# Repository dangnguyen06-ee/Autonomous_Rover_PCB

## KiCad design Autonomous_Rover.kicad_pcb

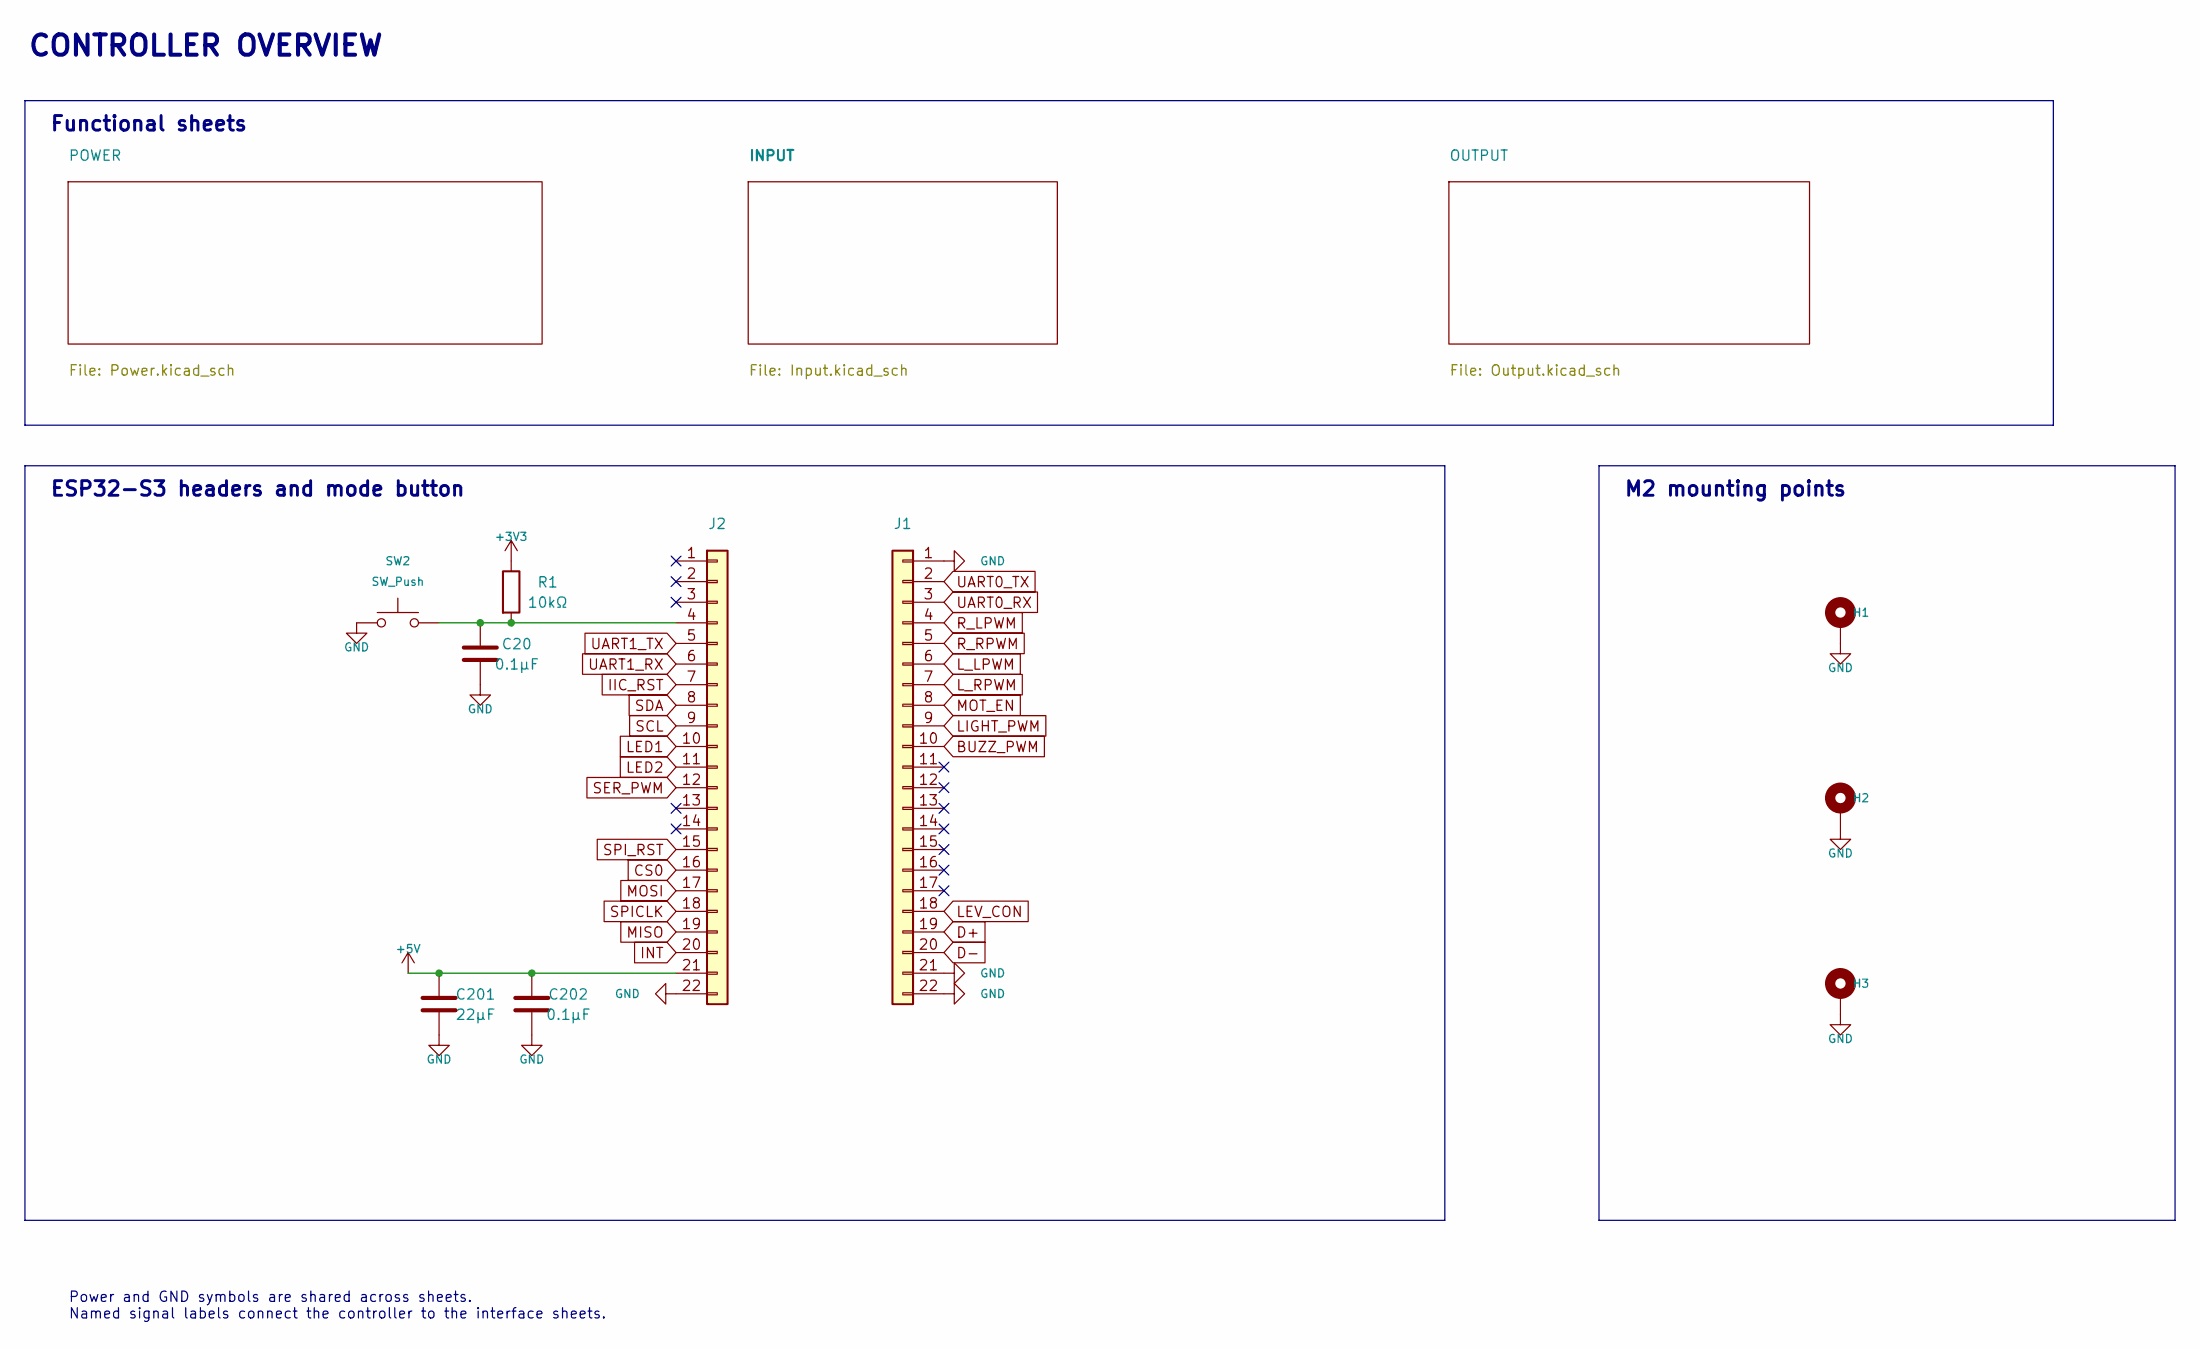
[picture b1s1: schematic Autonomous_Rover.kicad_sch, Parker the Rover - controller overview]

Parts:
C20, C202: 0.1µF; C_0805_2012Metric_Pad1.18x1.45mm_HandSolder
C201: 22µF; C_0805_2012Metric_Pad1.18x1.45mm_HandSolder
H1, H2, H3: M2; MountingHole_2.2mm_M2_ISO7380_Pad
J1: ESP32_R; PinSocket_1x22_P2.54mm_Vertical
J2: ESP32_L; PinSocket_1x22_P2.54mm_Vertical
R1: 10kΩ; R_0805_2012Metric_Pad1.20x1.40mm_HandSolder
SW2: SW_Push; SW_SPST_TS-1088-xR020

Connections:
+3V3: R1.1; also elsewhere on the board
+5V: C201.2, C202.2, J2.21; also elsewhere on the board
BUZZ_PWM: J1.10; also elsewhere on the board
CS0: J2.16; also elsewhere on the board
D+: J1.19; also elsewhere on the board
D-: J1.20; also elsewhere on the board
GND: C20.1, C201.1, C202.1, H1.1 (1_1), H2.1 (1_1), H3.1 (1_1), J1.1, J1.21, J1.22, J2.22, SW2.1; also elsewhere on the board
IIC_RST: J2.7; also elsewhere on the board
INT: J2.20; also elsewhere on the board
LED1: J2.10; also elsewhere on the board
LED2: J2.11; also elsewhere on the board
LEV_CON: J1.18; also elsewhere on the board
LIGHT_PWM: J1.9; also elsewhere on the board
L_LPWM: J1.6; also elsewhere on the board
L_RPWM: J1.7; also elsewhere on the board
MISO: J2.19; also elsewhere on the board
MOSI: J2.17; also elsewhere on the board
MOT_EN: J1.8; also elsewhere on the board
unnamed: C20.2, J2.4, R1.2, SW2.2
R_LPWM: J1.4; also elsewhere on the board
R_RPWM: J1.5; also elsewhere on the board
SCL: J2.9; also elsewhere on the board
SDA: J2.8; also elsewhere on the board
SER_PWM: J2.12; also elsewhere on the board
SPICLK: J2.18; also elsewhere on the board
SPI_RST: J2.15; also elsewhere on the board
UART0_RX: J1.3; also elsewhere on the board
UART0_TX: J1.2; also elsewhere on the board
UART1_RX: J2.6; also elsewhere on the board
UART1_TX: J2.5; also elsewhere on the board

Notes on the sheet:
M2 mounting points
Functional sheets
ESP32-S3 headers and mode button
CONTROLLER OVERVIEW
Power and GND symbols are shared across sheets. Named signal labels connect the controller to the interface sheets.

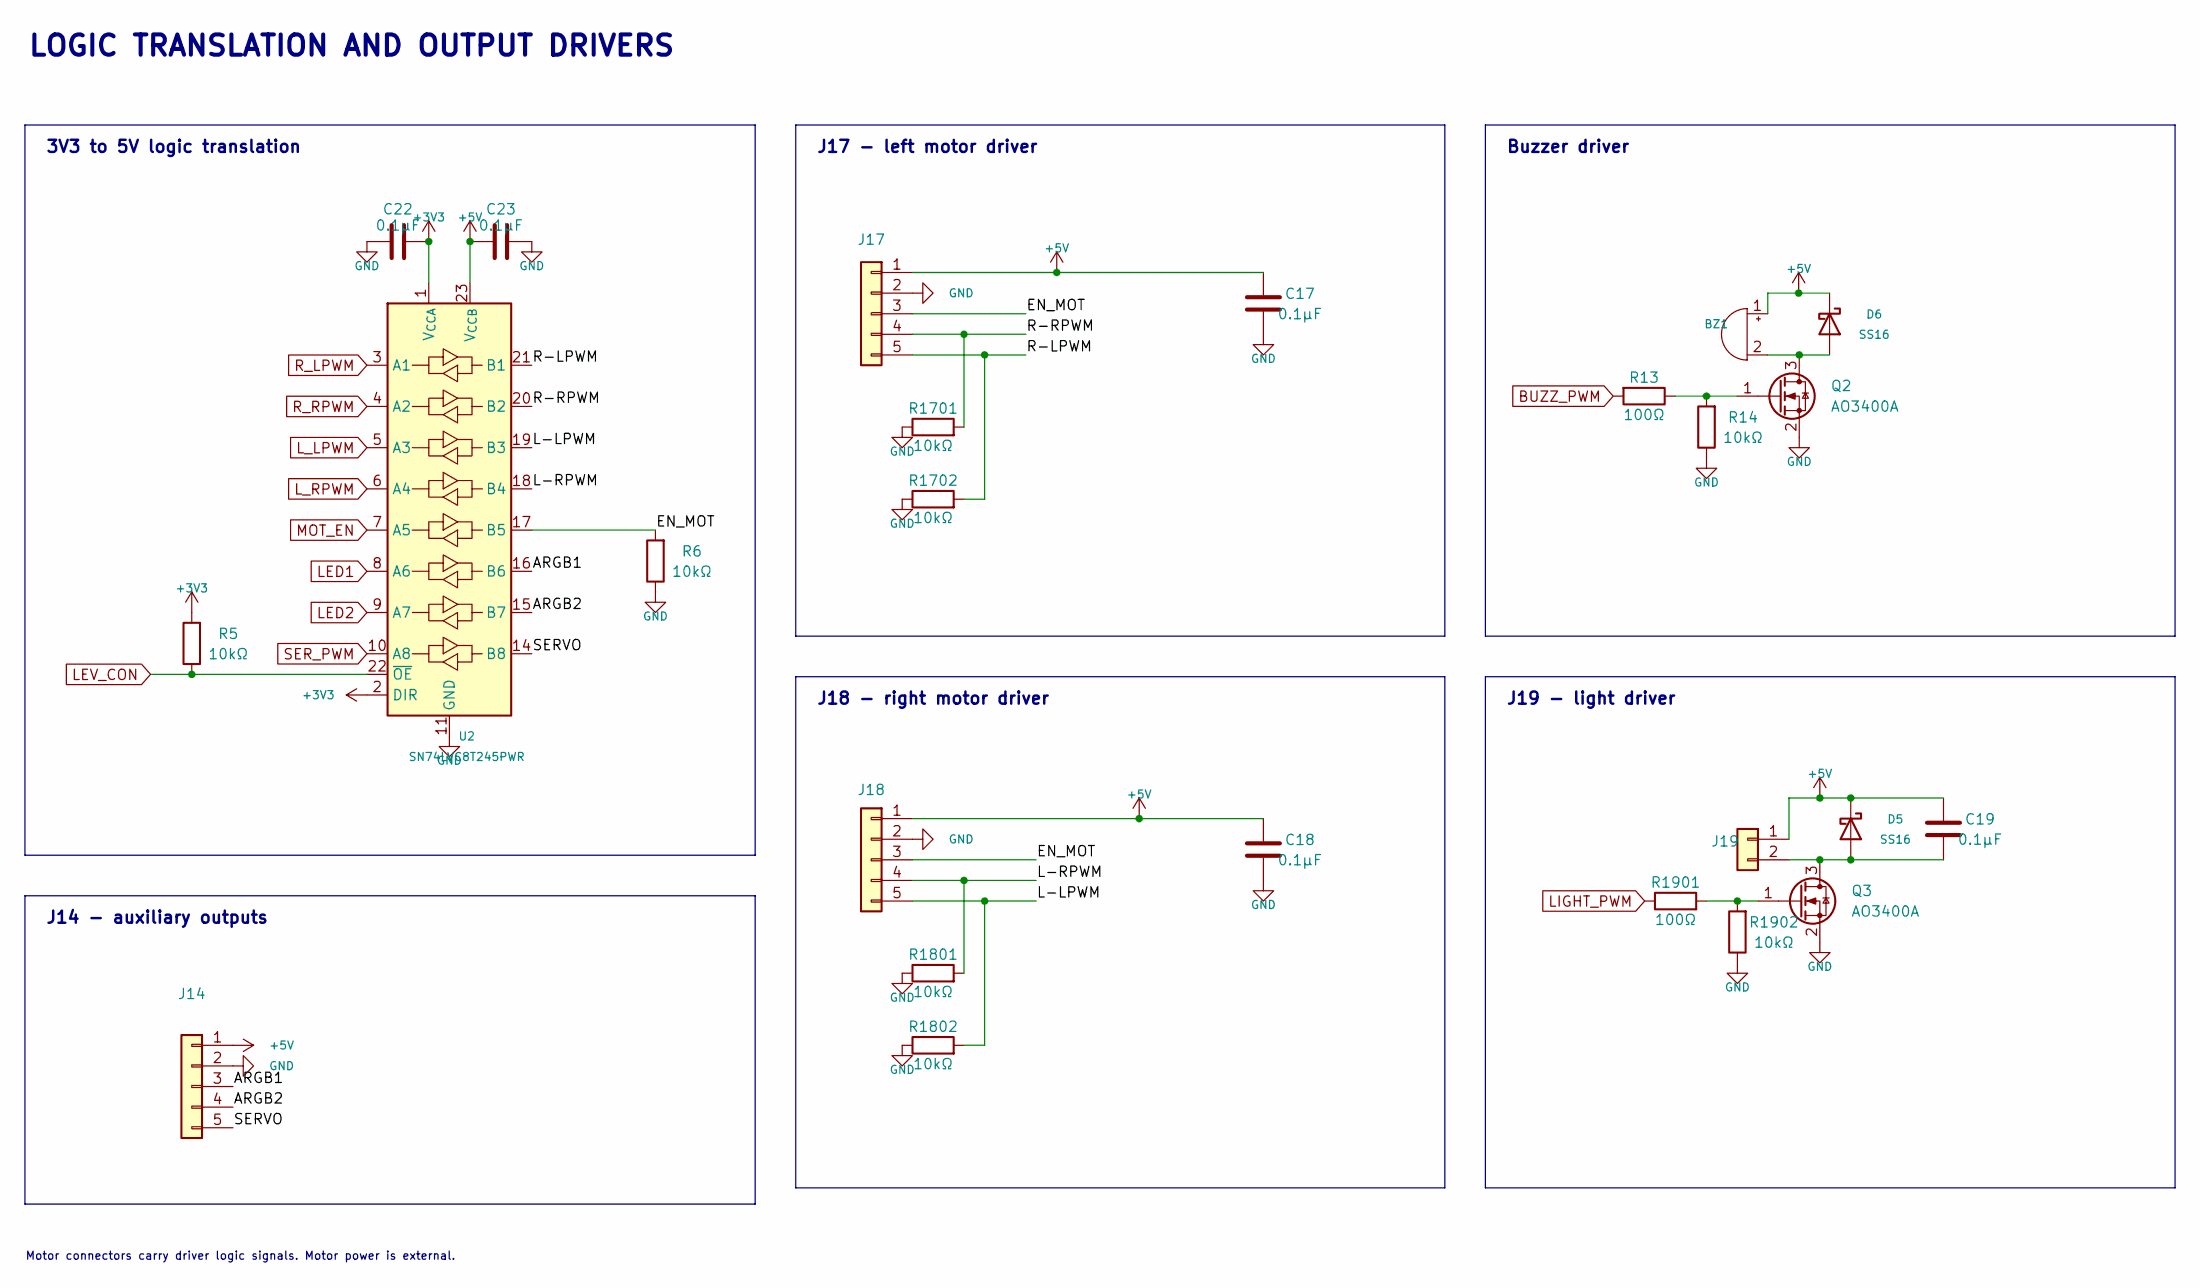
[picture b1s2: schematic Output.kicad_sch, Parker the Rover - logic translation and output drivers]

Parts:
BZ1: Buzzer; Buzzer_12x9.5RM7.6
C17, C18, C19, C22, C23: 0.1µF; C_0805_2012Metric_Pad1.18x1.45mm_HandSolder
D5, D6: SS16; D_SMA
J14: 5V_Con; JST_XH_B5B-XH-A_1x05_P2.50mm_Vertical
J17: L_MOT; JST_XH_B5B-XH-A_1x05_P2.50mm_Vertical
J18: R_MOT; JST_XH_B5B-XH-A_1x05_P2.50mm_Vertical
J19: BEAM_LIGHT; JST_XH_B2B-XH-A_1x02_P2.50mm_Vertical
Q2, Q3: AO3400A; SOT-23
R5, R6, R14, R1701, R1702, R1801, R1802, R1902: 10kΩ; R_0805_2012Metric_Pad1.20x1.40mm_HandSolder
R13, R1901: 100Ω; R_0805_2012Metric_Pad1.20x1.40mm_HandSolder
U2: SN74LVC8T245PWR; TSSOP-24_4.4x7.8mm_P0.65mm

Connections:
+3V3: C22.2, R5.2, U2.1 (V_{CCA}), U2.2 (DIR); also elsewhere on the board
+5V: BZ1.1 (+), C17.2, C18.2, C19.1, C23.2, D5.1 (K), D6.1 (K), J14.1, J17.1, J18.1, J19.1, U2.23 (V_{CCB}), U2.24 (V_{CCB}); also elsewhere on the board
/OUTPUT/ARGB1: J14.3, U2.16 (B6)
/OUTPUT/ARGB2: J14.4, U2.15 (B7)
/OUTPUT/EN_MOT: J17.3, J18.3, R6.2, U2.17 (B5)
/OUTPUT/L-LPWM: J18.5, R1802.2, U2.19 (B3)
/OUTPUT/L-RPWM: J18.4, R1801.2, U2.18 (B4)
/OUTPUT/R-LPWM: J17.5, R1702.2, U2.21 (B1)
/OUTPUT/R-RPWM: J17.4, R1701.2, U2.20 (B2)
/OUTPUT/SERVO: J14.5, U2.14 (B8)
BUZZ_PWM: R13.2; also elsewhere on the board
GND: C17.1, C18.1, C22.1, C23.1, J14.2, J17.2, J18.2, Q2.2 (S), Q3.2 (S), R6.1, R14.1, R1701.1, R1702.1, R1801.1, R1802.1, R1902.1, U2.11 (GND), U2.12 (GND), U2.13 (GND); also elsewhere on the board
LED1: U2.8 (A6); also elsewhere on the board
LED2: U2.9 (A7); also elsewhere on the board
LEV_CON: R5.1, U2.22 (~OE); also elsewhere on the board
LIGHT_PWM: R1901.1; also elsewhere on the board
L_LPWM: U2.5 (A3); also elsewhere on the board
L_RPWM: U2.6 (A4); also elsewhere on the board
MOT_EN: U2.7 (A5); also elsewhere on the board
unnamed: BZ1.2 (-), D6.2 (A), Q2.3 (D)
unnamed: C19.2, D5.2 (A), J19.2, Q3.3 (D)
unnamed: Q2.1 (G), R13.1, R14.2
unnamed: Q3.1 (G), R1901.2, R1902.2
R_LPWM: U2.3 (A1); also elsewhere on the board
R_RPWM: U2.4 (A2); also elsewhere on the board
SER_PWM: U2.10 (A8); also elsewhere on the board

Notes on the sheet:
3V3 to 5V logic translation
Motor connectors carry driver logic signals. Motor power is external.
J17 - left motor driver
J14 - auxiliary outputs
J18 - right motor driver
LOGIC TRANSLATION AND OUTPUT DRIVERS
J19 - light driver
Buzzer driver

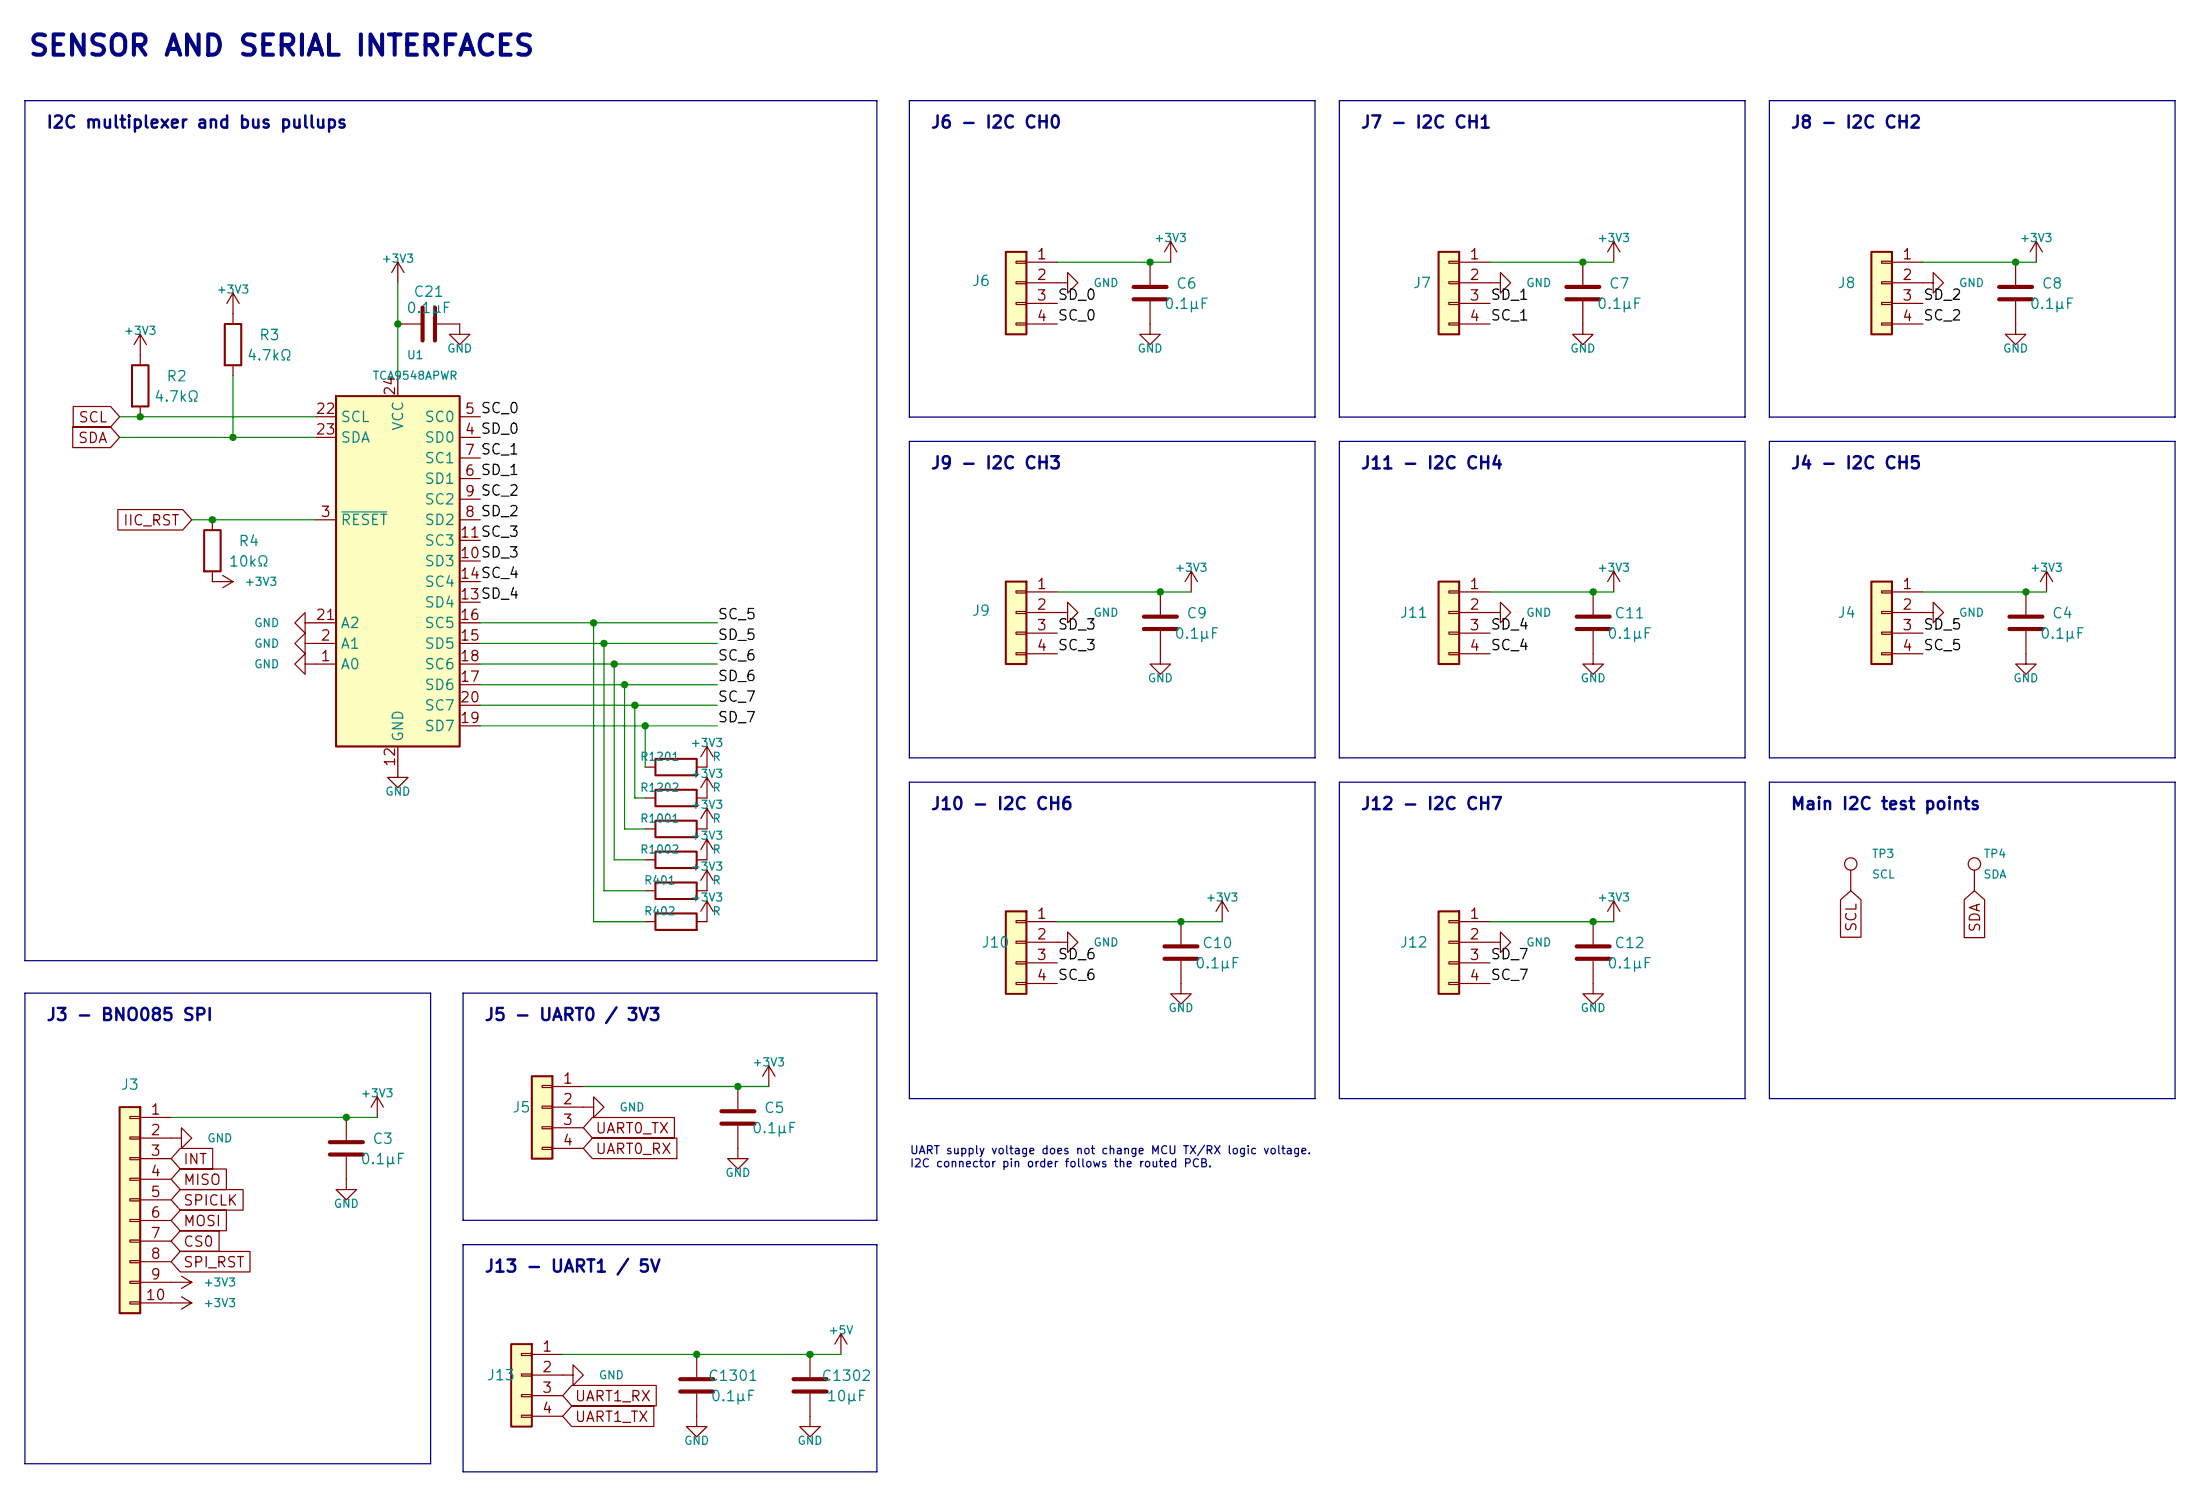
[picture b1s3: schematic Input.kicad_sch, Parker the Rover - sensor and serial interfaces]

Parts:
C3, C4, C5, C6, C7, C8, C9, C10, C11, C12, C21, C1301: 0.1µF; C_0805_2012Metric_Pad1.18x1.45mm_HandSolder
C1302: 10µF; C_0805_2012Metric_Pad1.18x1.45mm_HandSolder
J3: BNO085; JST_XH_B10B-XH-A_1x10_P2.50mm_Vertical
J4: I2C_CH5; JST_XH_B4B-XH-A_1x04_P2.50mm_Vertical
J5: UART0_3V; JST_XH_B4B-XH-A_1x04_P2.50mm_Vertical
J6: I2C_CH0; JST_XH_B4B-XH-A_1x04_P2.50mm_Vertical
J7: I2C_CH1; JST_XH_B4B-XH-A_1x04_P2.50mm_Vertical
J8: I2C_CH2; JST_XH_B4B-XH-A_1x04_P2.50mm_Vertical
J9: I2C_CH3; JST_XH_B4B-XH-A_1x04_P2.50mm_Vertical
J10: I2C_CH6; JST_XH_B4B-XH-A_1x04_P2.50mm_Vertical
J11: I2C_CH4; JST_XH_B4B-XH-A_1x04_P2.50mm_Vertical
J12: I2C_CH7; JST_XH_B4B-XH-A_1x04_P2.50mm_Vertical
J13: UART1_5V; JST_XH_B4B-XH-A_1x04_P2.50mm_Vertical
R2, R3: 4.7kΩ; R_0805_2012Metric_Pad1.20x1.40mm_HandSolder
R4: 10kΩ; R_0805_2012Metric_Pad1.20x1.40mm_HandSolder
R401, R402, R1001, R1002, R1201, R1202: R; R_0805_2012Metric_Pad1.20x1.40mm_HandSolder
TP3: SCL; TestPoint_Loop_D1.80mm_Drill1.0mm_Beaded
TP4: SDA; TestPoint_Loop_D1.80mm_Drill1.0mm_Beaded
U1: TCA9548APWR; TSSOP-24_4.4x7.8mm_P0.65mm

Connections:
+3V3: C3.1, C4.1, C5.2, C6.1, C7.1, C8.1, C9.1, C10.1, C11.1, C12.1, C21.1, J3.1, J3.9, J3.10, J4.1, J5.1, J6.1, J7.1, J8.1, J9.1, J10.1, J11.1, J12.1, R2.1, R3.1, R4.2, R401.2, R402.2, R1001.2, R1002.2, R1201.2, R1202.2, U1.24 (VCC); also elsewhere on the board
+5V: C1301.2, C1302.2, J13.1; also elsewhere on the board
/INPUT/SC_0: J6.4, U1.5 (SC0)
/INPUT/SC_1: J7.4, U1.7 (SC1)
/INPUT/SC_2: J8.4, U1.9 (SC2)
/INPUT/SC_3: J9.4, U1.11 (SC3)
/INPUT/SC_4: J11.4, U1.14 (SC4)
/INPUT/SC_5: J4.4, R402.1, U1.16 (SC5)
/INPUT/SC_6: J10.4, R1002.1, U1.18 (SC6)
/INPUT/SC_7: J12.4, R1202.1, U1.20 (SC7)
/INPUT/SD_0: J6.3, U1.4 (SD0)
/INPUT/SD_1: J7.3, U1.6 (SD1)
/INPUT/SD_2: J8.3, U1.8 (SD2)
/INPUT/SD_3: J9.3, U1.10 (SD3)
/INPUT/SD_4: J11.3, U1.13 (SD4)
/INPUT/SD_5: J4.3, R401.1, U1.15 (SD5)
/INPUT/SD_6: J10.3, R1001.1, U1.17 (SD6)
/INPUT/SD_7: J12.3, R1201.1, U1.19 (SD7)
CS0: J3.7; also elsewhere on the board
GND: C3.2, C4.2, C5.1, C6.2, C7.2, C8.2, C9.2, C10.2, C11.2, C12.2, C21.2, C1301.1, C1302.1, J3.2, J4.2, J5.2, J6.2, J7.2, J8.2, J9.2, J10.2, J11.2, J12.2, J13.2, U1.1 (A0), U1.2 (A1), U1.12 (GND), U1.21 (A2); also elsewhere on the board
IIC_RST: R4.1, U1.3 (~RESET); also elsewhere on the board
INT: J3.3; also elsewhere on the board
MISO: J3.4; also elsewhere on the board
MOSI: J3.6; also elsewhere on the board
SCL: R2.2, TP3.1 (1_1), U1.22 (SCL); also elsewhere on the board
SDA: R3.2, TP4.1 (1_1), U1.23 (SDA); also elsewhere on the board
SPICLK: J3.5; also elsewhere on the board
SPI_RST: J3.8; also elsewhere on the board
UART0_RX: J5.4; also elsewhere on the board
UART0_TX: J5.3; also elsewhere on the board
UART1_RX: J13.3; also elsewhere on the board
UART1_TX: J13.4; also elsewhere on the board

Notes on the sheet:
J7 - I2C CH1
J12 - I2C CH7
J8 - I2C CH2
J3 - BNO085 SPI
UART supply voltage does not change MCU TX/RX logic voltage. I2C connector pin order follows the routed PCB.
J5 - UART0 / 3V3
J9 - I2C CH3
J6 - I2C CH0
Main I2C test points
J4 - I2C CH5
J11 - I2C CH4
I2C multiplexer and bus pullups
SENSOR AND SERIAL INTERFACES
J13 - UART1 / 5V
J10 - I2C CH6

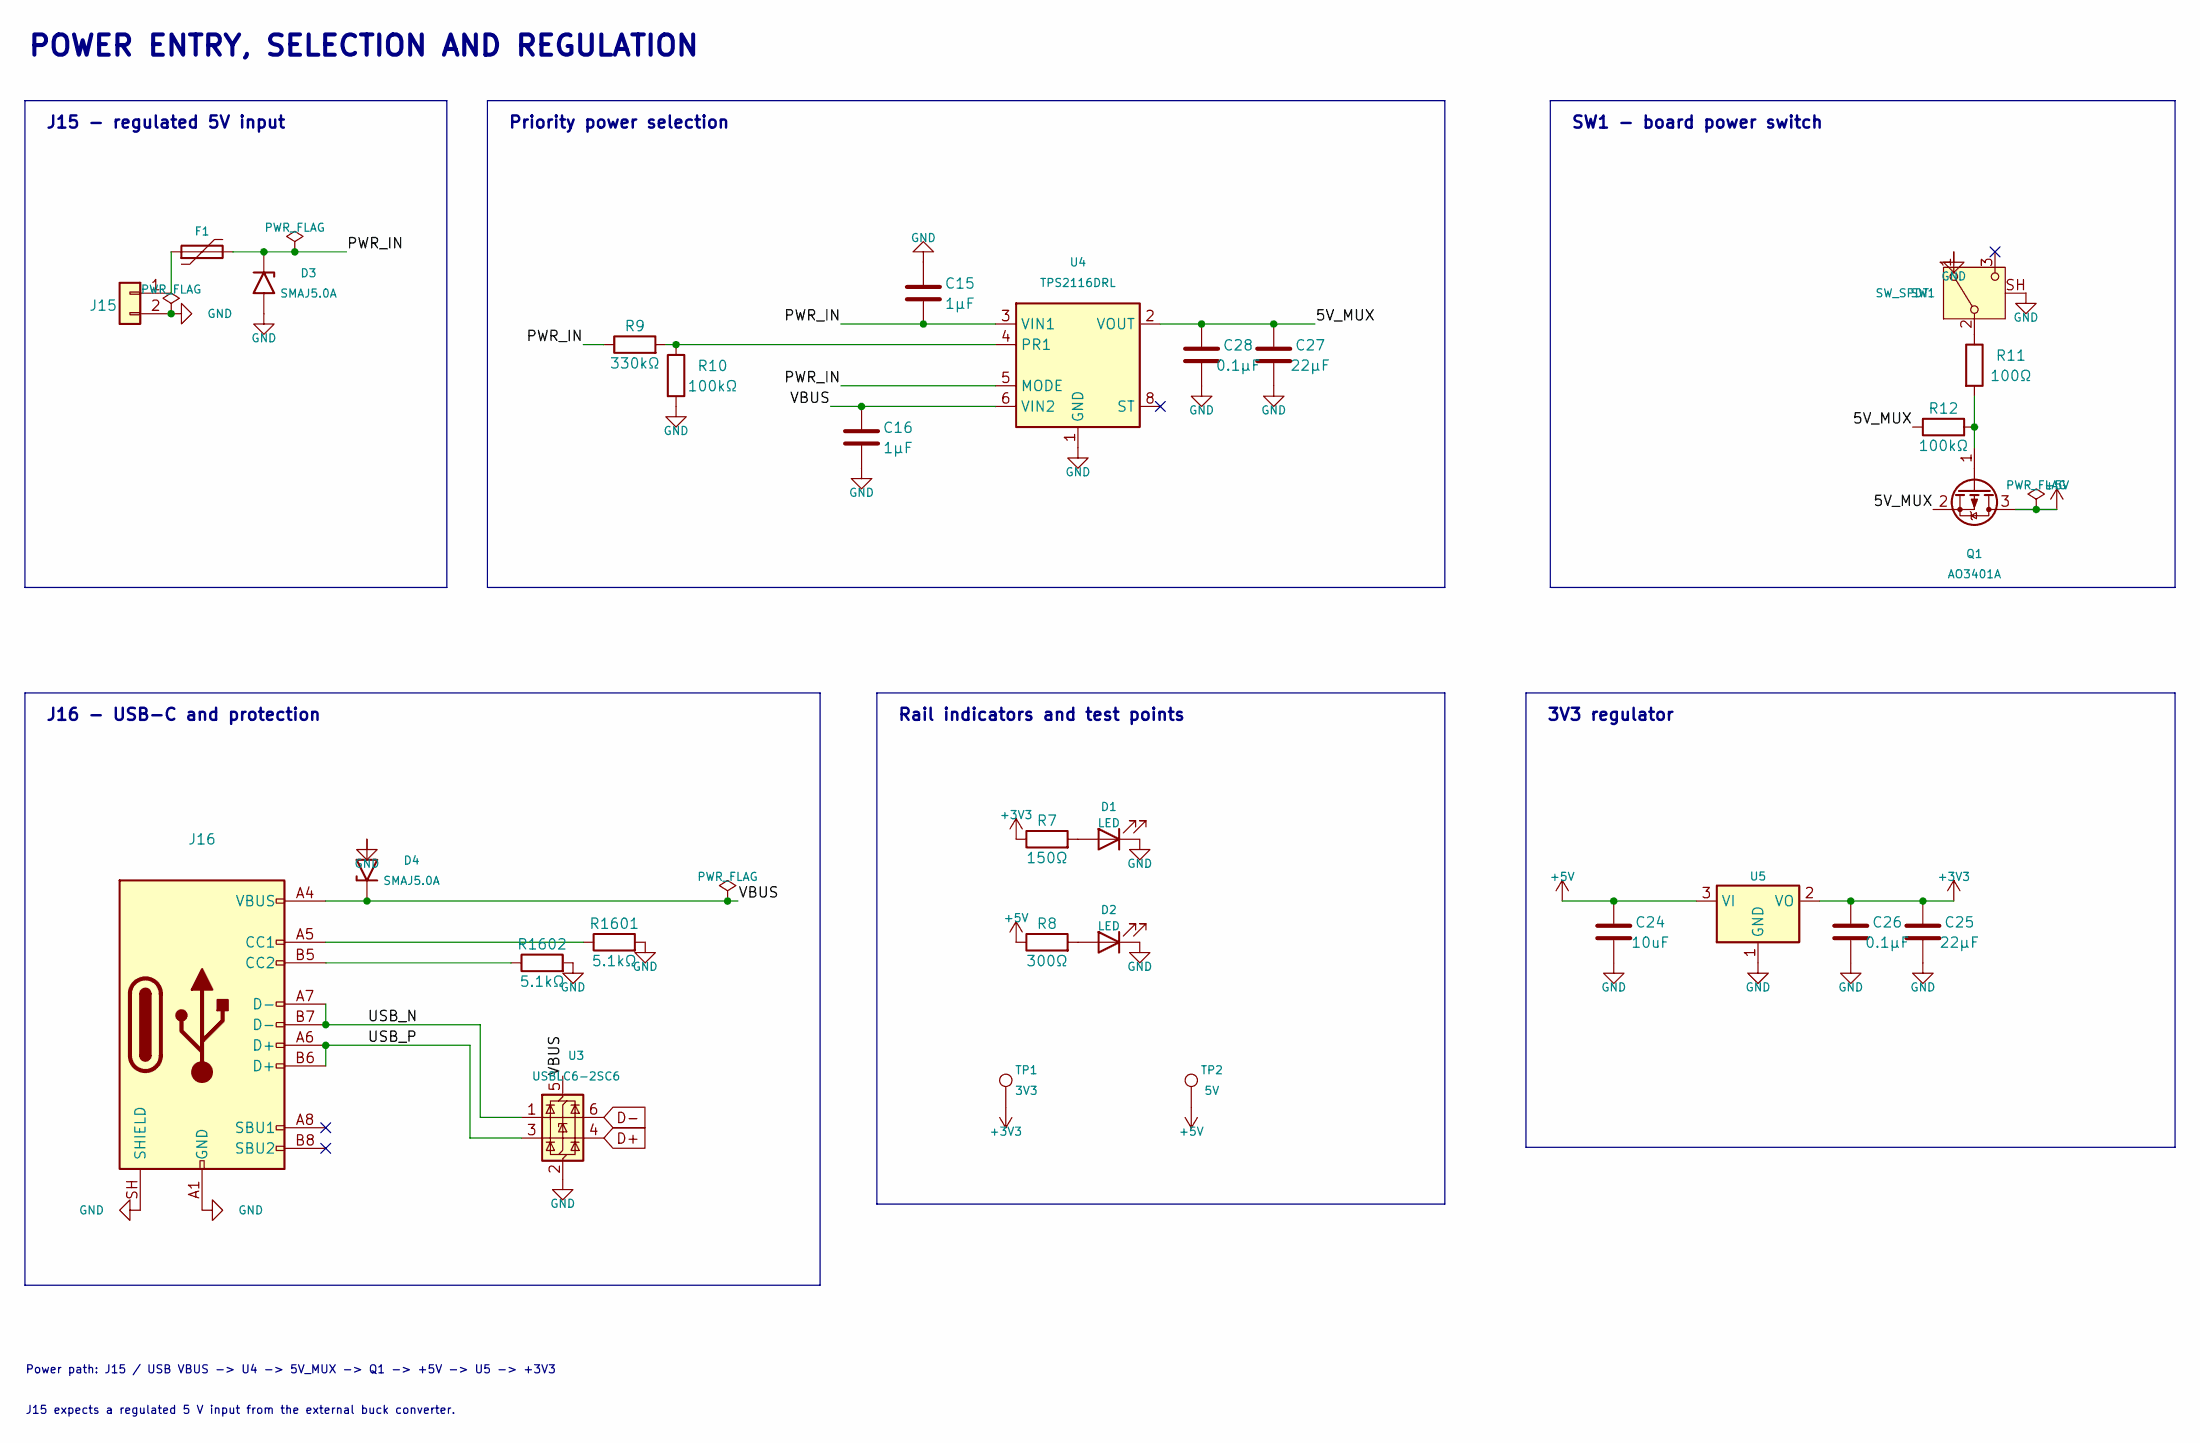
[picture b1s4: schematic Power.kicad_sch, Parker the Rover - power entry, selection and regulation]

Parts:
C15, C16: 1µF; C_0805_2012Metric_Pad1.18x1.45mm_HandSolder
C24: 10uF; C_0805_2012Metric_Pad1.18x1.45mm_HandSolder
C25, C27: 22µF; C_0805_2012Metric_Pad1.18x1.45mm_HandSolder
C26, C28: 0.1µF; C_0805_2012Metric_Pad1.18x1.45mm_HandSolder
D1, D2: LED; LED_0805_2012Metric_Pad1.15x1.40mm_HandSolder
D3, D4: SMAJ5.0A; D_SMA
F1: 1.85A Hold / 3.7A Trip; Fuse_2920_7451Metric_Pad2.10x5.45mm_HandSolder
J15: POWER; Molex_Micro-Fit_3.0_43045-0200_2x01_P3.00mm_Horizontal
J16: USB_C_Receptacle_USB2.0_16P; USB_C_Receptacle_HRO_TYPE-C-31-M-12
Q1: AO3401A; SOT-23
R7: 150Ω; R_0805_2012Metric_Pad1.20x1.40mm_HandSolder
R8: 300Ω; R_0805_2012Metric_Pad1.20x1.40mm_HandSolder
R9: 330kΩ; R_0805_2012Metric_Pad1.20x1.40mm_HandSolder
R10, R12: 100kΩ; R_0805_2012Metric_Pad1.20x1.40mm_HandSolder
R11: 100Ω; R_0805_2012Metric_Pad1.20x1.40mm_HandSolder
R1601, R1602: 5.1kΩ; R_0805_2012Metric_Pad1.20x1.40mm_HandSolder
SW1: SW_SPDT; SW_SPDT_Shouhan_MSK12C02
TP1: 3V3; TestPoint_Loop_D1.80mm_Drill1.0mm_Beaded
TP2: 5V; TestPoint_Loop_D1.80mm_Drill1.0mm_Beaded
U3: USBLC6-2SC6; SOT-23-6_Handsoldering
U4: TPS2116DRL; SOT-583-8
U5: AMS1117-3.3; SOT-223-3_TabPin2

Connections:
+3V3: C25.1, C26.2, R7.1, TP1.1 (1_1), U5.2 (VO); also elsewhere on the board
+5V: C24.1, Q1.3 (D), R8.1, TP2.1 (1_1), U5.3 (VI); also elsewhere on the board
/POWER/5V_MUX: C27.1, C28.2, Q1.2 (S), R12.1, U4.2 (VOUT), U4.7 (VOUT)
/POWER/PWR_IN: C15.2, D3.1 (A1), F1.2, R9.1, U4.3 (VIN1), U4.5 (MODE)
/POWER/USB_N: J16.A7 (D-), J16.B7 (D-), U3.1 (I/O1)
/POWER/USB_P: J16.A6 (D+), J16.B6 (D+), U3.3 (I/O2)
/POWER/VBUS: C16.2, D4.1 (A1), J16.A4 (VBUS), J16.A9 (VBUS), J16.B4 (VBUS), J16.B9 (VBUS), U3.5 (VBUS), U4.6 (VIN2)
D+: U3.4 (I/O2); also elsewhere on the board
D-: U3.6 (I/O1); also elsewhere on the board
GND: C15.1, C16.1, C24.2, C25.2, C26.1, C27.2, C28.1, D1.1 (K), D2.1 (K), D3.2 (A2), D4.2 (A2), J15.2, J16.A1 (GND), J16.A12 (GND), J16.B1 (GND), J16.B12 (GND), J16.SH (SHIELD), R10.2, R1601.2, R1602.2, SW1.1 (A), SW1.SH, U3.2 (GND), U4.1 (GND), U5.1 (GND); also elsewhere on the board
unnamed: D1.2 (A), R7.2
unnamed: D2.2 (A), R8.2
unnamed: F1.1, J15.1
unnamed: J16.A5 (CC1), R1601.1
unnamed: J16.B5 (CC2), R1602.1
unnamed: Q1.1 (G), R11.2, R12.2
unnamed: R11.1, SW1.2 (B)
unnamed: R9.2, R10.1, U4.4 (PR1)

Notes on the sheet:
SW1 - board power switch
Power path: J15 / USB VBUS -> U4 -> 5V_MUX -> Q1 -> +5V -> U5 -> +3V3
J15 expects a regulated 5 V input from the external buck converter.
Priority power selection
3V3 regulator
J15 - regulated 5V input
Rail indicators and test points
J16 - USB-C and protection
POWER ENTRY, SELECTION AND REGULATION

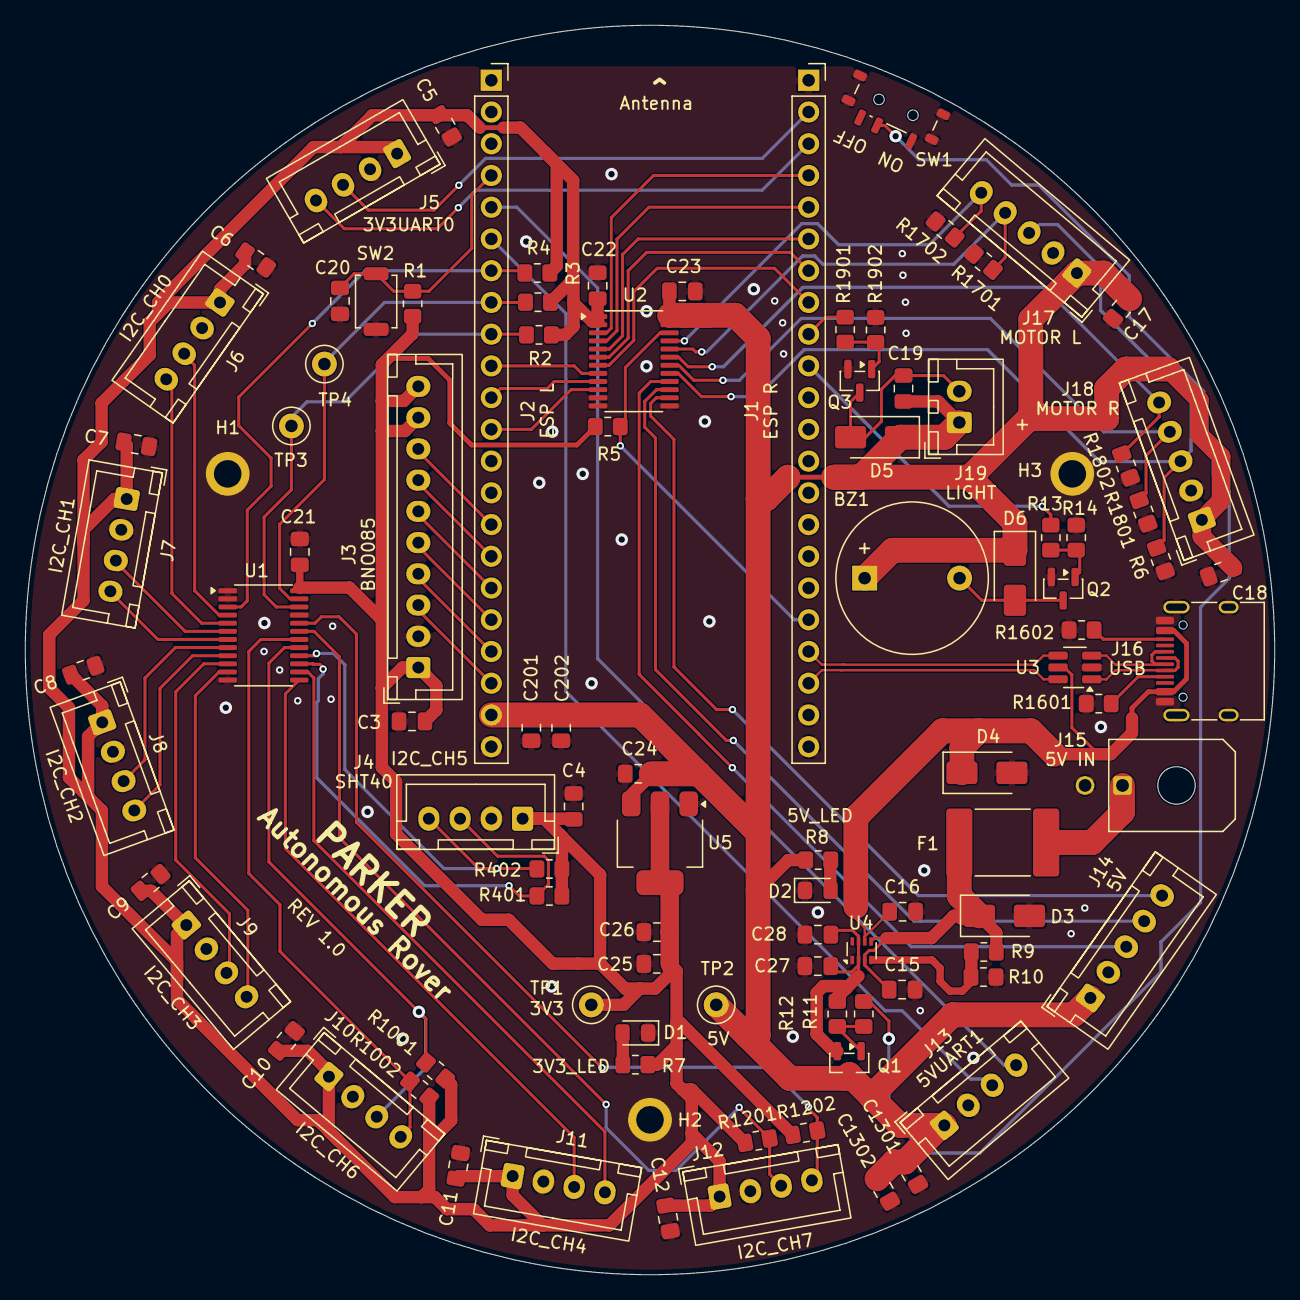
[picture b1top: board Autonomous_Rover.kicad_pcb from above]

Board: 2 copper layers, 100.0 x 100.0 mm, 100 parts (0 on the bottom side), 71 nets.
